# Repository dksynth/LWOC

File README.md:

# LWOC
Ornament and Crime for Loudest Warning Format

please note that there are two different spacings in use. 

The "broken grid" variant pushes two rows a bit closer together towards the screen at the bottom. This preserves the spacing of the top row at the cost of a crowded set of jacks nearer the encoders and  screen. 

IN ALMOST ALL CASES (unless you've made your own panels) you will want to use the main files found in the main repository.

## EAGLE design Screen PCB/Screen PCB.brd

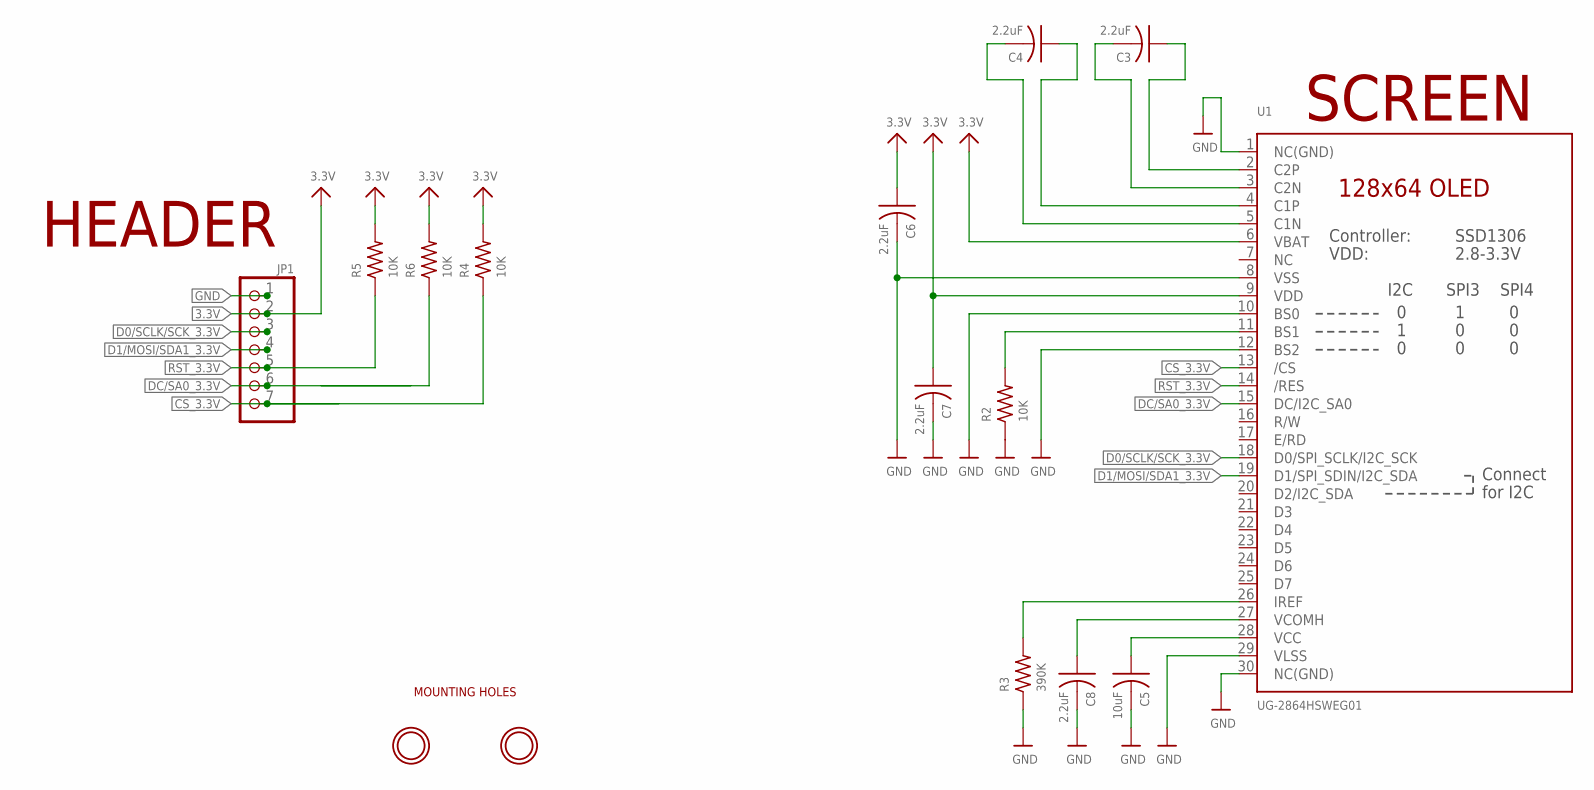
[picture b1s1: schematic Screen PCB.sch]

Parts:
C3, C4, C6, C7, C8: 2.2uF; C0805
C5: 10uF; C0805
JP1: HEADER-1X7ROUND; 1X07_ROUND
R2, R4, R5, R6: 10K; R0805
R3: 390K; R0805
U1: UG-2864HSWEG01; UG-2864HSWEG01_1.3_WRAPAROUND
U$23, U$26: MOUNTINGHOLE2.5; MOUNTINGHOLE_2.5_PLATED

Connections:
3.3V: C6.1, C7.1, JP1.2, R4.2, R5.2, R6.2, U1.6 (VBAT), U1.9 (VDD)
CS_3.3V: JP1.7, R4.1, U1.13 (/CS)
D0/SCLK/SCK_3.3V: JP1.3, U1.18 (D0/SPI_SCLK/I2C_SCK)
D1/MOSI/SDA1_3.3V: JP1.4, U1.19 (D1/SPI_SDIN/I2C_SDA)
DC/SA0_3.3V: JP1.6, R6.1, U1.15 (DC/I2C_SA0)
GND: C5.2, C6.2, C7.2, C8.2, JP1.1, R2.1, R3.1, U1.1 (NC(GND)), U1.8 (VSS), U1.10 (BS0), U1.12 (BS2), U1.29 (VLSS), U1.30 (NC(GND))
unnamed: R2.2, U1.11 (BS1)
unnamed: R3.2, U1.26 (IREF)
unnamed: C4.1, U1.4 (C1P)
unnamed: C3.2, U1.3 (C2N)
unnamed: C3.1, U1.2 (C2P)
unnamed: C4.2, U1.5 (C1N)
unnamed: C5.1, U1.28 (VCC)
unnamed: C8.1, U1.27 (VCOMH)
RST_3.3V: JP1.5, R5.1, U1.14 (/RES)

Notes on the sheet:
MOUNTING HOLES
SCREEN
HEADER

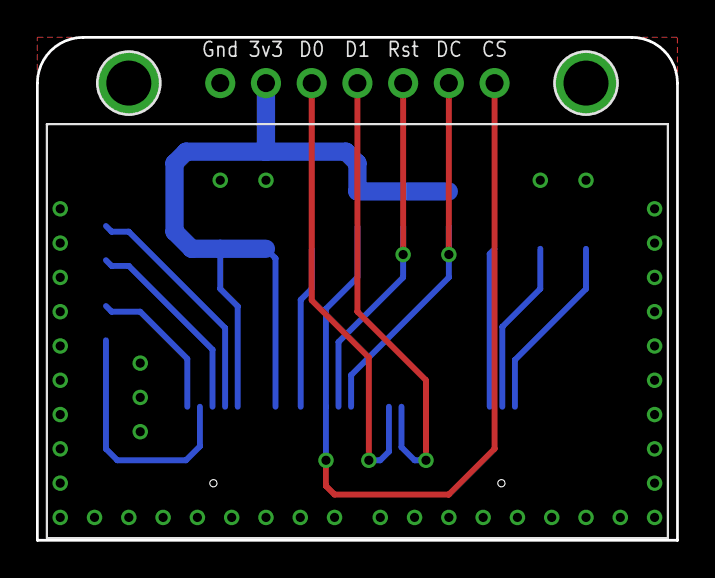
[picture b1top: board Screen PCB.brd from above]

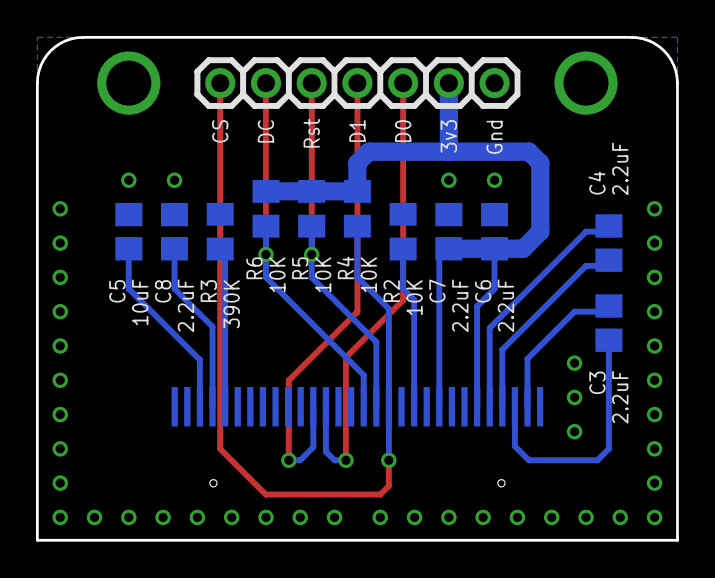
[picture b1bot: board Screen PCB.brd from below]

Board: 2 copper layers, 35.6 x 27.9 mm, 15 parts (11 on the bottom side), 15 nets.

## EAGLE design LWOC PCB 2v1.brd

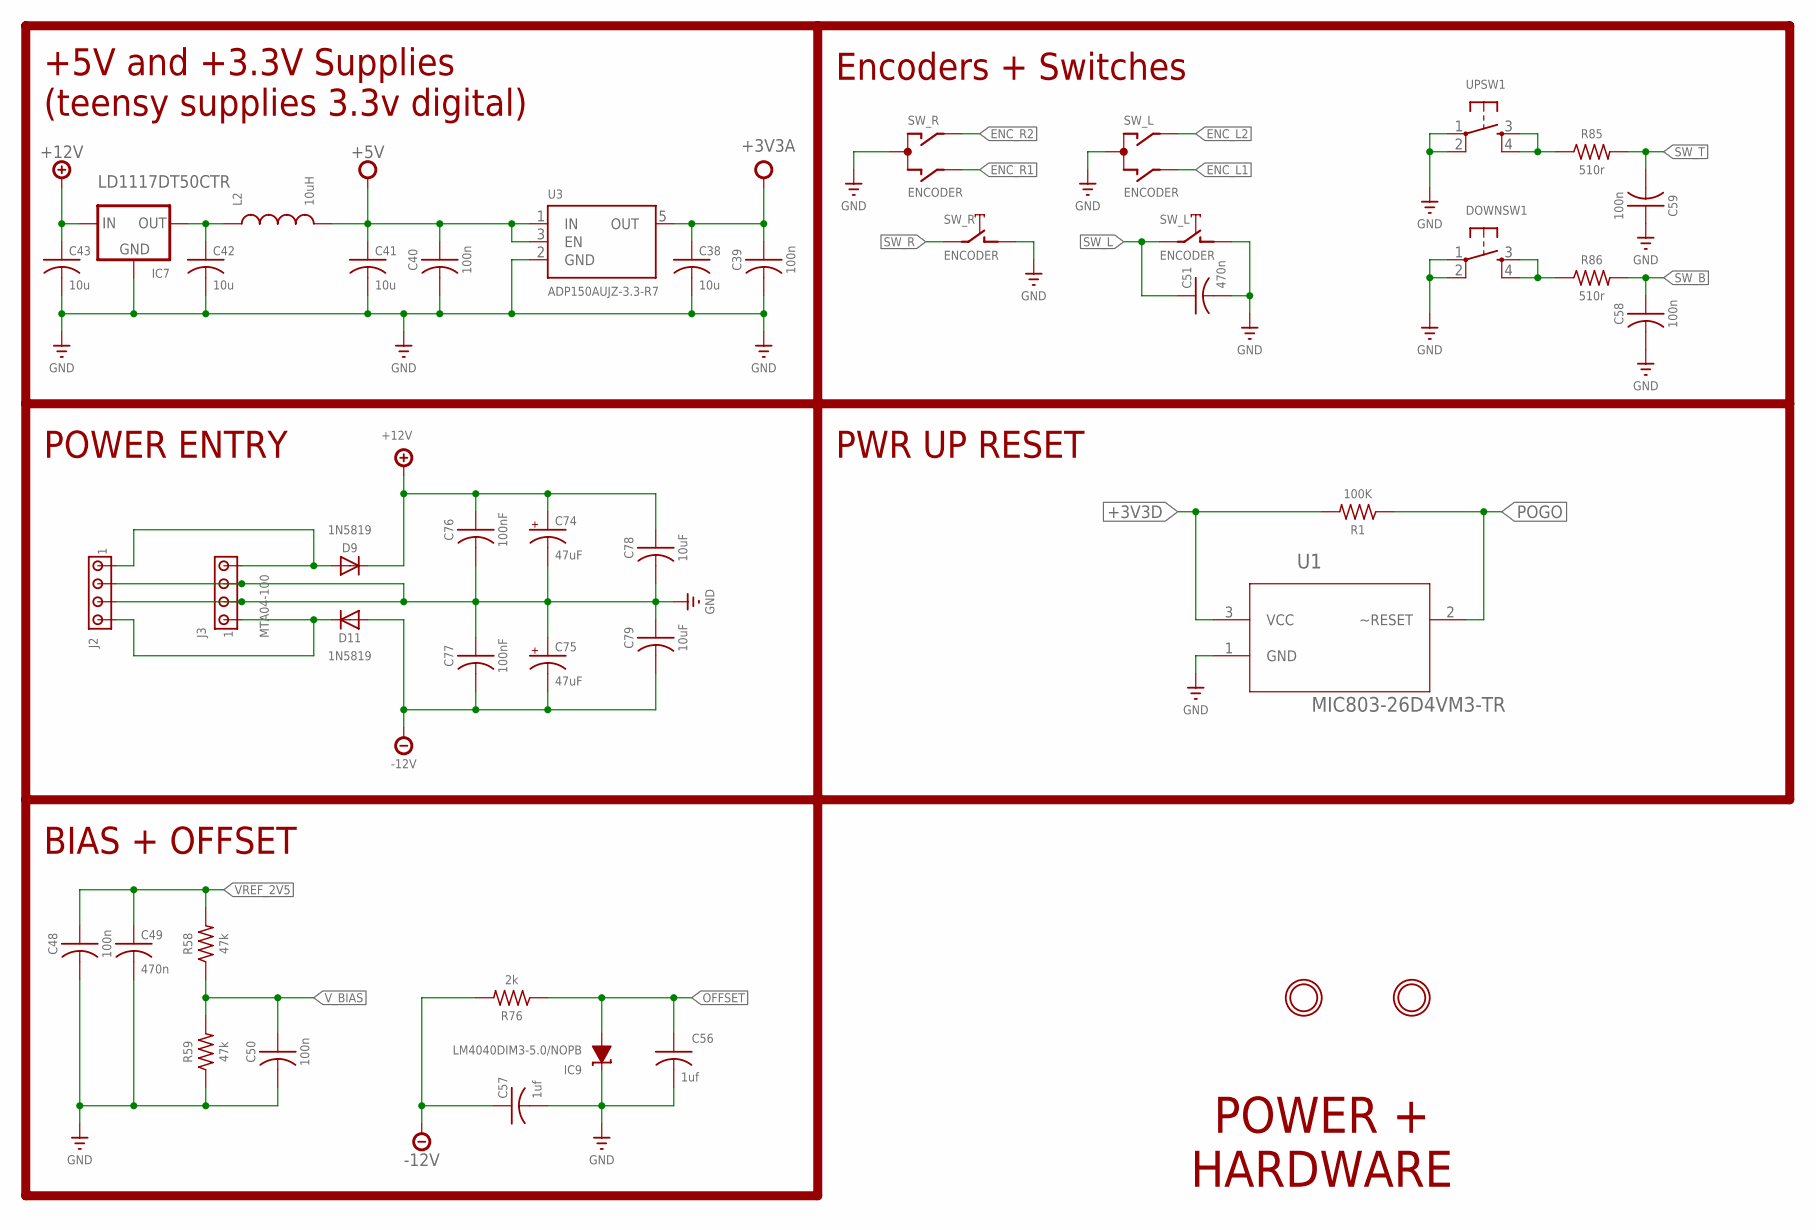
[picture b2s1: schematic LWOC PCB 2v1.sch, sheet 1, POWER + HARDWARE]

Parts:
C38, C41, C42, C43: 10u; C1206K
C39, C40, C48, C50, C58, C59: 100n; RCL_C0603K
C49: 470n; RCL_C0603K
C51: 470n; C0805K
C56, C57: 1uf; C0805K
C74, C75: 47uF; RCL_E2,5-6
C76, C77: 100nF; RCL_C0603K
C78, C79: 10uF; RCL_C1210
D9, D11: 1N5819; DIODE_SOD323-W
DOWNSW1: SPARKFUN_TAC_SWITCHPTH; SPARKFUN_TACTILE-PTH
IC7: LD1117DT50CTR; TO252
IC9: LM4040DIM3-5.0/NOPB; DBZ_R-PDSO-G3
J2: MTA04-156; 1X4MTA
J3: MTA04-100; 1X04MTA
L2: 10uH; 1210
R1: 100K; RCL_R0603
R58, R59: 47k; RCL_R0603
R76: 2k; RCL_R0603
R85, R86: 510r; RCL_R0603
SW_L: ENCODER; OG-ENCODER_ALPS_EC12E_SW
SW_R: ENCODER; OG-ENCODER_ALPS_EC12E_SW
U1: MIC803-26D4VM3-TR; SOT95P232X110-3N
U3: ADP150AUJZ-3.3-R7; SOT23-5
U$23, U$26: MOUNTINGHOLE2.5; MOUNTINGHOLE_2.5_PLATED
UPSW1: SPARKFUN_TAC_SWITCHPTH; SPARKFUN_TACTILE-PTH

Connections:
+3V3A: C38.1, C39.1, U3.5 (OUT); also elsewhere on the board
+3V3D: R1.2, U1.3 (VCC); also elsewhere on the board
+5V: C40.1, C41.1, L2.2, U3.1 (IN), U3.3 (EN); also elsewhere on the board
+12V: C43.1, C74.+, C76.1, C78.1, D9.C, IC7.2 (IN); also elsewhere on the board
-12V: C57.1, C75.-, C77.2, C79.2, D11.A, R76.2; also elsewhere on the board
ENC_L1: SW_L.B; also elsewhere on the board
ENC_L2: SW_L.A; also elsewhere on the board
ENC_R1: SW_R.B; also elsewhere on the board
ENC_R2: SW_R.A; also elsewhere on the board
GND: C38.2, C39.2, C40.2, C41.2, C42.2, C43.2, C48.2, C49.2, C50.2, C51.2, C56.2, C57.2, C58.2, C59.1, C74.-, C75.+, C76.2, C77.1, C78.2, C79.1, DOWNSW1.1, DOWNSW1.2, IC7.1 (GND), IC9.1 (C), J2.2, J2.3, J3.2 (3), J3.3 (2), R59.1, SW_L.C, SW_L.D (1), SW_R.C, SW_R.D (1), U1.1 (GND), U3.2 (GND), UPSW1.1, UPSW1.2; also elsewhere on the board
unnamed: C42.1, IC7.3 (OUT), L2.1
unnamed: R85.1, UPSW1.3, UPSW1.4
unnamed: DOWNSW1.3, DOWNSW1.4, R86.1
unnamed: D11.C, J2.4, J3.4 (1)
unnamed: D9.A, J2.1, J3.1 (4)
OFFSET: C56.1, IC9.2 (A), R76.1; also elsewhere on the board
POGO: R1.1, U1.2 (~RESET)
SW_B: C58.1, R86.2; also elsewhere on the board
SW_L: C51.1, SW_L.E (2); also elsewhere on the board
SW_R: SW_R.E (2); also elsewhere on the board
SW_T: C59.2, R85.2; also elsewhere on the board
VREF_2V5: C48.1, C49.1, R58.2; also elsewhere on the board
V_BIAS: C50.1, R58.1, R59.2; also elsewhere on the board

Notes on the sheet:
POWER + HARDWARE
+5V and +3.3V Supplies (teensy supplies 3.3v digital)
Encoders + Switches
PWR UP RESET
POWER ENTRY
BIAS + OFFSET

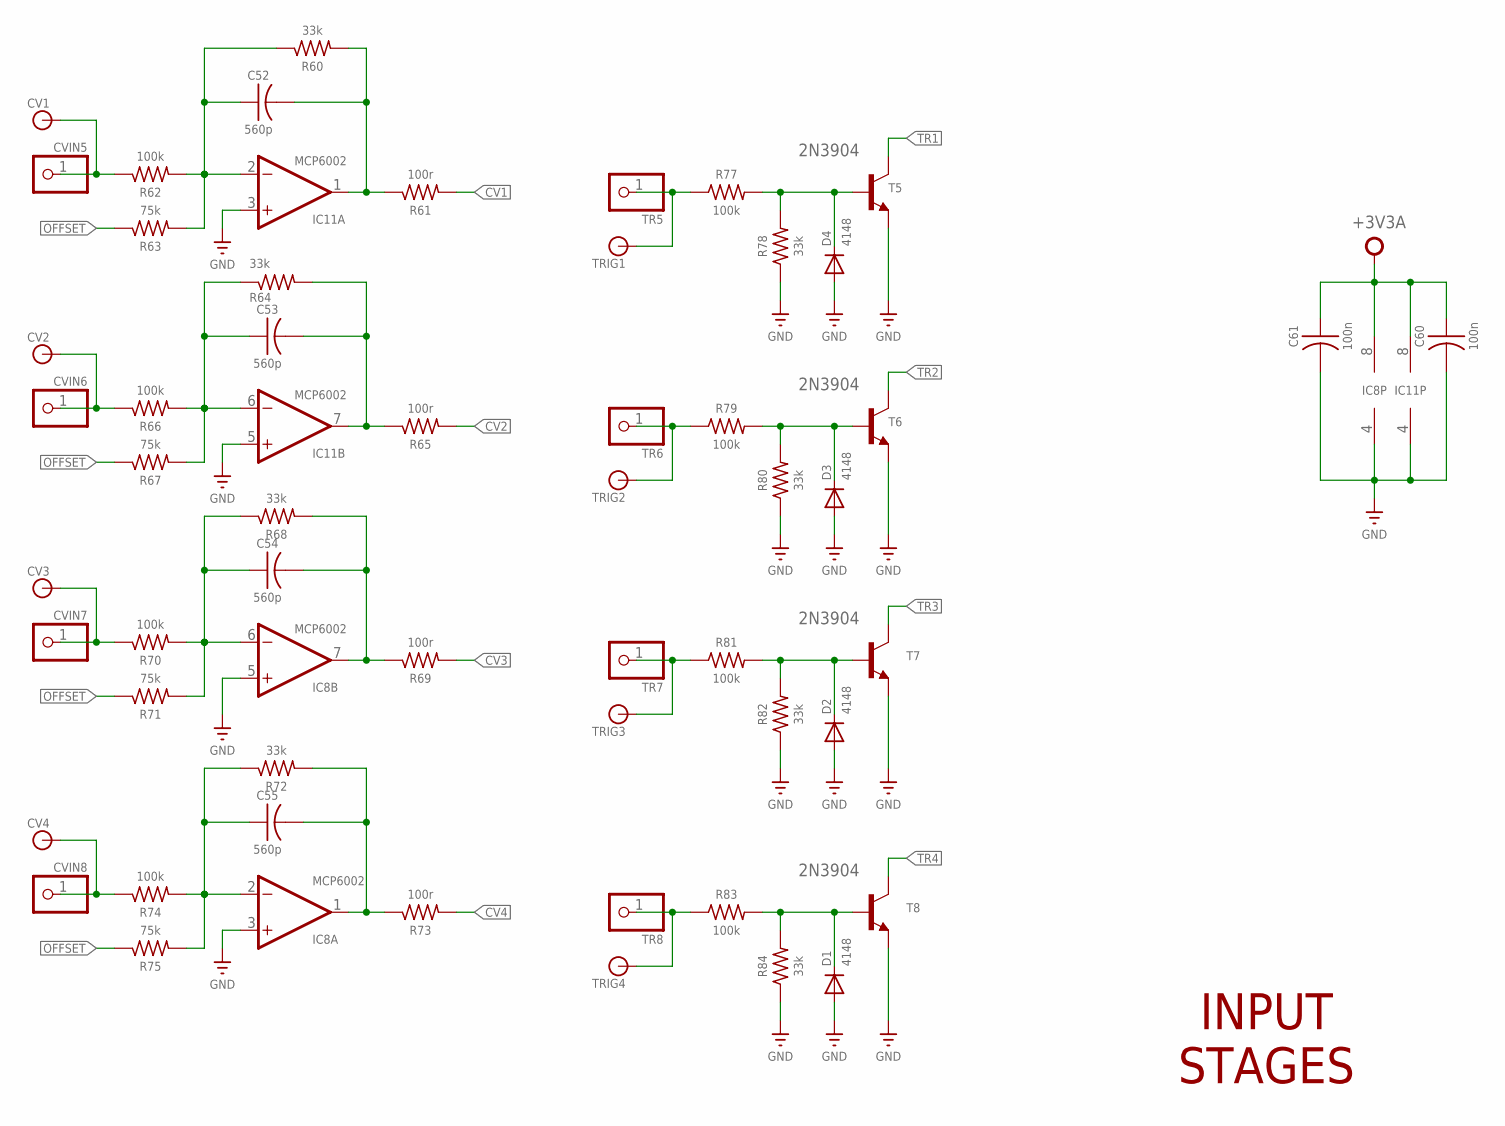
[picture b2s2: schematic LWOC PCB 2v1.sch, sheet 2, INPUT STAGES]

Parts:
C52, C53, C54, C55: 560p; RCL_C0603K
C60, C61: 100n; RCL_C0603K
CV1, CV2, CV3, CV4: BANANA_CONN
CVIN5, CVIN6, CVIN7, CVIN8: PINHD-1X1; 1X01
D1, D2, D3, D4: 4148; DIODE_SOD323-W
IC8, IC11: MCP6002; GM-ICS_SO08
R60, R64, R68, R72, R78, R80, R82, R84: 33k; RCL_R0603
R61, R65, R69, R73: 100r; RCL_R0603
R62, R66, R70, R74, R77, R79, R81, R83: 100k; RCL_R0603
R63, R67, R71, R75: 75k; RCL_R0603
T5, T6, T7, T8: 2N3904; TRANSISTOR_SOT23-BEC
TR5, TR6, TR7, TR8: PINHD-1X1; 1X01
TRIG1, TRIG2, TRIG3, TRIG4: BANANA_CONN

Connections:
+3V3A: C60.1, C61.1, IC8.8 (V+), IC11.8 (V+); also elsewhere on the board
CV1: R61.2; also elsewhere on the board
CV2: R65.2; also elsewhere on the board
CV3: R69.2; also elsewhere on the board
CV4: R73.2; also elsewhere on the board
GND: C60.2, C61.2, D1.A, D2.A, D3.A, D4.A, IC8.3 (+IN), IC8.4 (V-), IC8.5 (+IN), IC11.3 (+IN), IC11.4 (V-), IC11.5 (+IN), R78.1, R80.1, R82.1, R84.1, T5.E, T6.E, T7.E, T8.E; also elsewhere on the board
unnamed: CV1.P$1, CVIN5.1, R62.1
unnamed: C52.1, IC11.2 (-IN), R60.1, R62.2, R63.2
unnamed: C52.2, IC11.1 (OUT), R60.2, R61.1
unnamed: CV2.P$1, CVIN6.1, R66.1
unnamed: C53.1, IC11.6 (-IN), R64.1, R66.2, R67.2
unnamed: C53.2, IC11.7 (OUT), R64.2, R65.1
unnamed: CV3.P$1, CVIN7.1, R70.1
unnamed: C54.1, IC8.6 (-IN), R68.1, R70.2, R71.2
unnamed: C54.2, IC8.7 (OUT), R68.2, R69.1
unnamed: CV4.P$1, CVIN8.1, R74.1
unnamed: C55.1, IC8.2 (-IN), R72.1, R74.2, R75.2
unnamed: C55.2, IC8.1 (OUT), R72.2, R73.1
unnamed: R77.1, TR5.1, TRIG1.P$1
unnamed: R79.1, TR6.1, TRIG2.P$1
unnamed: R81.1, TR7.1, TRIG3.P$1
unnamed: D1.C, R83.2, R84.2, T8.B
unnamed: D2.C, R81.2, R82.2, T7.B
unnamed: D3.C, R79.2, R80.2, T6.B
unnamed: D4.C, R77.2, R78.2, T5.B
unnamed: R83.1, TR8.1, TRIG4.P$1
OFFSET: R63.1, R67.1, R71.1, R75.1; also elsewhere on the board
TR1: T5.C; also elsewhere on the board
TR2: T6.C; also elsewhere on the board
TR3: T7.C; also elsewhere on the board
TR4: T8.C; also elsewhere on the board

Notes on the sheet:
INPUT STAGES

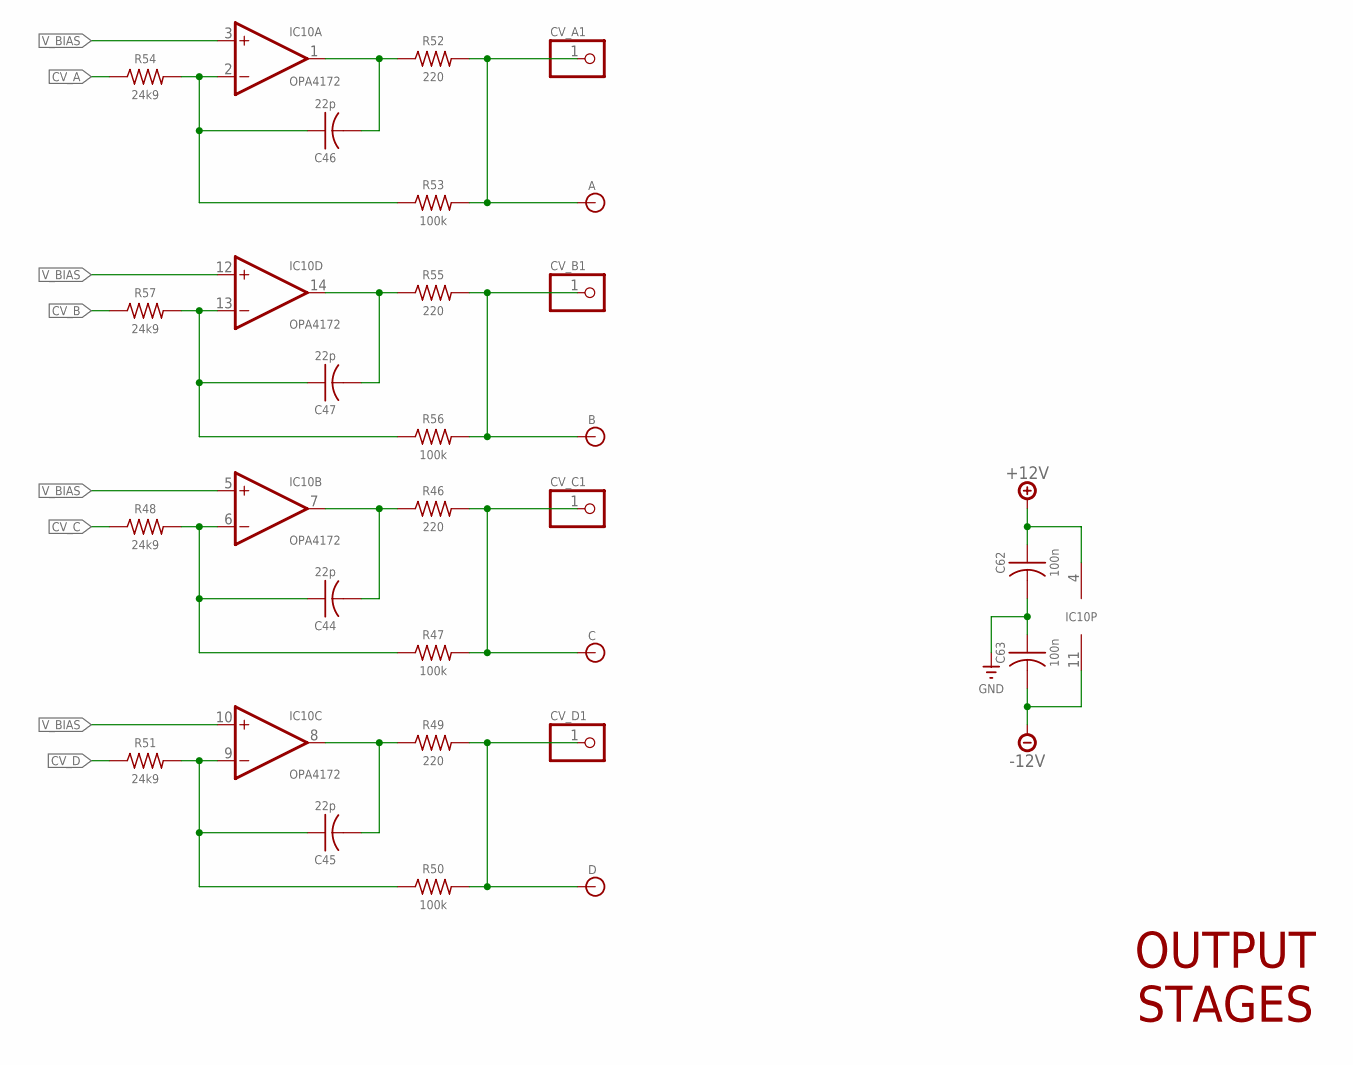
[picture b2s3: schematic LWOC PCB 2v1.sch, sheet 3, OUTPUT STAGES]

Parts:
A: BANANA_CONN
B: BANANA_CONN
C: BANANA_CONN
C44, C45, C46, C47: 22p; RCL_C0603K
C62, C63: 100n; RCL_C0603K
CV_A1: PINHD-1X1; 1X01
CV_B1: PINHD-1X1; 1X01
CV_C1: PINHD-1X1; 1X01
CV_D1: PINHD-1X1; 1X01
D: BANANA_CONN
IC10: OPA4172; GM-ICS_SO14
R46, R49, R52, R55: 220; RCL_R0603
R47, R50, R53, R56: 100k; RCL_R0603
R48, R51, R54, R57: 24k9; RCL_R0603

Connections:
+12V: C62.1, IC10.4 (V+); also elsewhere on the board
-12V: C63.2, IC10.11 (V-); also elsewhere on the board
CV_A: R54.1; also elsewhere on the board
CV_B: R57.1; also elsewhere on the board
CV_C: R48.1; also elsewhere on the board
CV_D: R51.1; also elsewhere on the board
GND: C62.2, C63.1; also elsewhere on the board
unnamed: C44.1, IC10.6 (-IN), R47.1, R48.2
unnamed: C44.2, IC10.7 (OUT), R46.1
unnamed: C45.1, IC10.9 (-IN), R50.1, R51.2
unnamed: C45.2, IC10.8 (OUT), R49.1
unnamed: C46.1, IC10.2 (-IN), R53.1, R54.2
unnamed: C46.2, IC10.1 (OUT), R52.1
unnamed: C47.1, IC10.13 (-IN), R56.1, R57.2
unnamed: C47.2, IC10.14 (OUT), R55.1
unnamed: B.P$1, CV_B1.1, R55.2, R56.2
unnamed: CV_D1.1, D.P$1, R49.2, R50.2
unnamed: A.P$1, CV_A1.1, R52.2, R53.2
unnamed: C.P$1, CV_C1.1, R46.2, R47.2
V_BIAS: IC10.3 (+IN), IC10.5 (+IN), IC10.10 (+IN), IC10.12 (+IN); also elsewhere on the board

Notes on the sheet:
OUTPUT STAGES

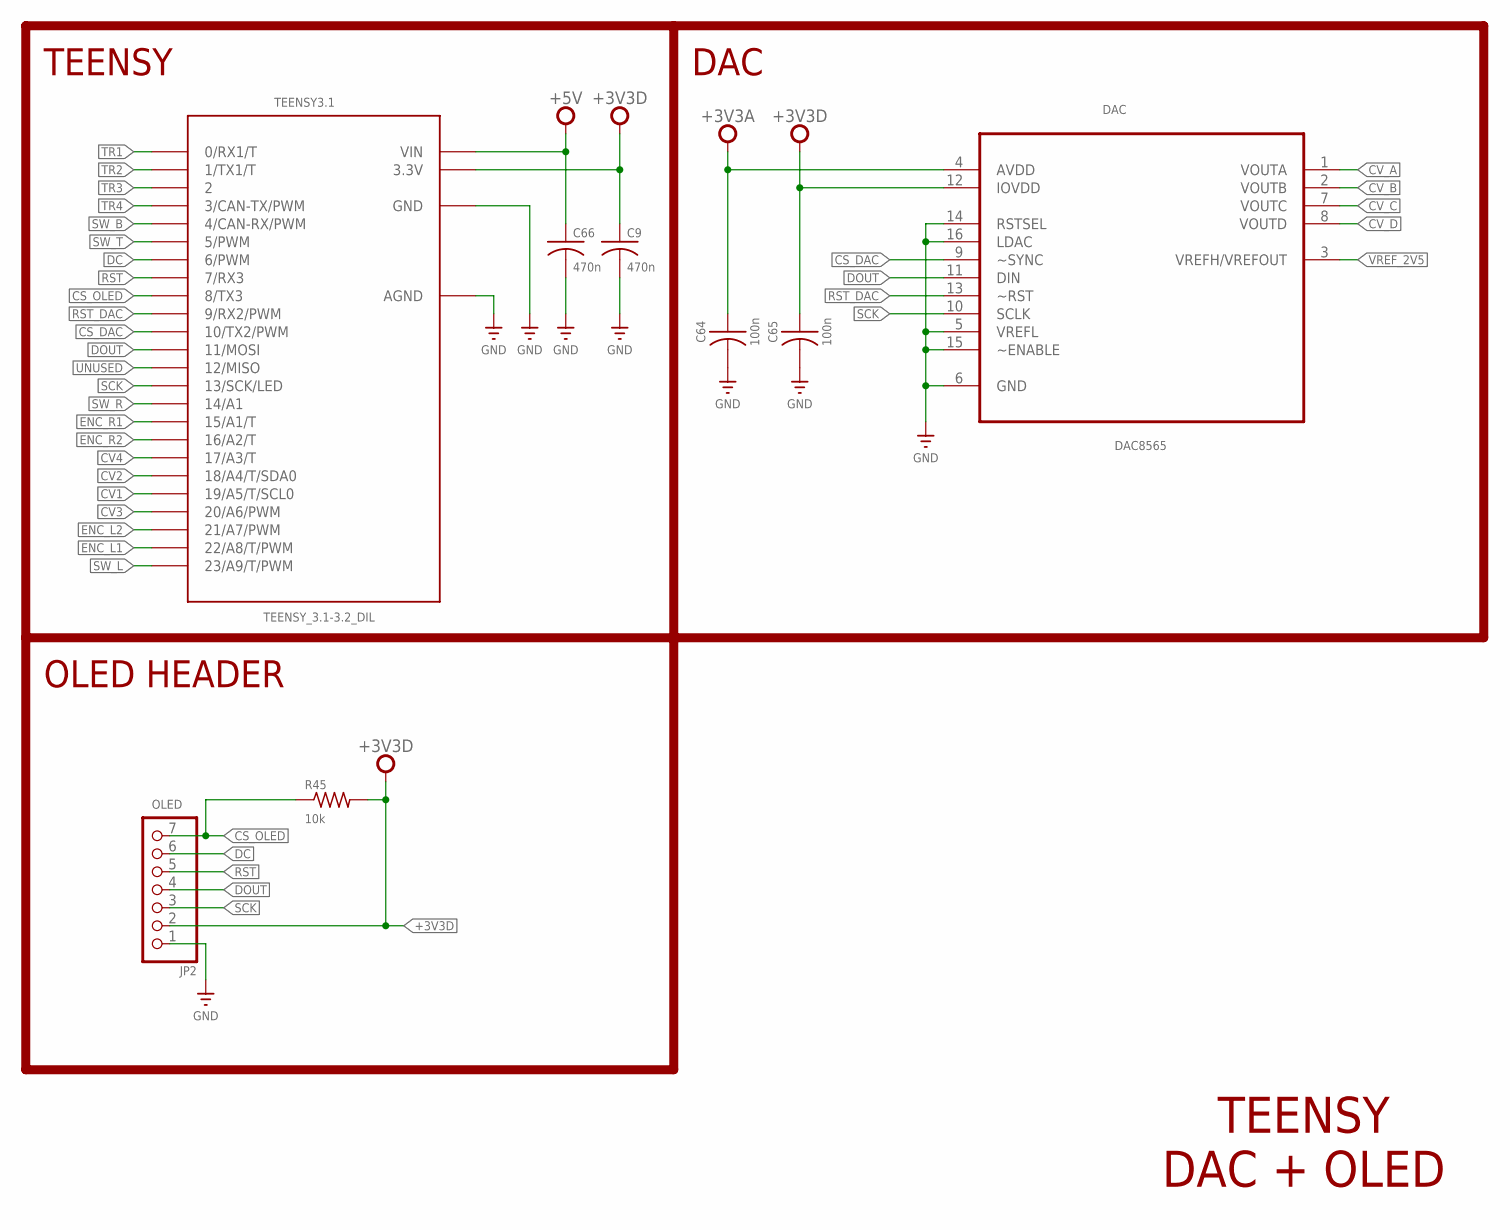
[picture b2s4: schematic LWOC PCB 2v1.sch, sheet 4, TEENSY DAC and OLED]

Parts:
C9, C66: 470n; C0805K
C64, C65: 100n; RCL_C0603K
DAC: DAC8565; SOP65P640X120-16N
JP2: OLED; 1X07-S
R45: 10k; M0805
TEENSY3.1: TEENSY_3.1-3.2_DIL; TEENSY_3.0-3.2&LC_DIL

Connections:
+3V3A: C64.1, DAC.4 (AVDD); also elsewhere on the board
+3V3D: C9.1, C65.1, DAC.12 (IOVDD), JP2.2, R45.2, TEENSY3.1.3.3V; also elsewhere on the board
+5V: C66.1, TEENSY3.1.VIN; also elsewhere on the board
CS_DAC: DAC.9 (~SYNC), TEENSY3.1.10 (10/TX2/PWM)
CS_OLED: JP2.7, R45.1, TEENSY3.1.8 (8/TX3)
CV1: TEENSY3.1.19/A5 (19/A5/T/SCL0); also elsewhere on the board
CV2: TEENSY3.1.18/A4 (18/A4/T/SDA0); also elsewhere on the board
CV3: TEENSY3.1.20/A6 (20/A6/PWM); also elsewhere on the board
CV4: TEENSY3.1.17/A3 (17/A3/T); also elsewhere on the board
CV_A: DAC.1 (VOUTA); also elsewhere on the board
CV_B: DAC.2 (VOUTB); also elsewhere on the board
CV_C: DAC.7 (VOUTC); also elsewhere on the board
CV_D: DAC.8 (VOUTD); also elsewhere on the board
DC: JP2.6, TEENSY3.1.6 (6/PWM)
DOUT: DAC.11 (DIN), JP2.4, TEENSY3.1.11 (11/MOSI)
ENC_L1: TEENSY3.1.22/A8 (22/A8/T/PWM); also elsewhere on the board
ENC_L2: TEENSY3.1.21/A7 (21/A7/PWM); also elsewhere on the board
ENC_R1: TEENSY3.1.15/A1 (15/A1/T); also elsewhere on the board
ENC_R2: TEENSY3.1.16/A2 (16/A2/T); also elsewhere on the board
GND: C9.2, C64.2, C65.2, C66.2, DAC.5 (VREFL), DAC.6 (GND), DAC.14 (RSTSEL), DAC.15 (~ENABLE), DAC.16 (LDAC), JP2.1, TEENSY3.1.AGND, TEENSY3.1.GND; also elsewhere on the board
RST: JP2.5, TEENSY3.1.7 (7/RX3)
RST_DAC: DAC.13 (~RST), TEENSY3.1.9 (9/RX2/PWM)
SCK: DAC.10 (SCLK), JP2.3, TEENSY3.1.13 (13/SCK/LED)
SW_B: TEENSY3.1.4 (4/CAN-RX/PWM); also elsewhere on the board
SW_L: TEENSY3.1.23/A9 (23/A9/T/PWM); also elsewhere on the board
SW_R: TEENSY3.1.14/A0 (14/A1); also elsewhere on the board
SW_T: TEENSY3.1.5 (5/PWM); also elsewhere on the board
TR1: TEENSY3.1.0 (0/RX1/T); also elsewhere on the board
TR2: TEENSY3.1.1 (1/TX1/T); also elsewhere on the board
TR3: TEENSY3.1.2; also elsewhere on the board
TR4: TEENSY3.1.3 (3/CAN-TX/PWM); also elsewhere on the board
UNUSED: TEENSY3.1.12 (12/MISO)
VREF_2V5: DAC.3 (VREFH/VREFOUT); also elsewhere on the board

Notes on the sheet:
TEENSY DAC + OLED
OLED HEADER
TEENSY
DAC

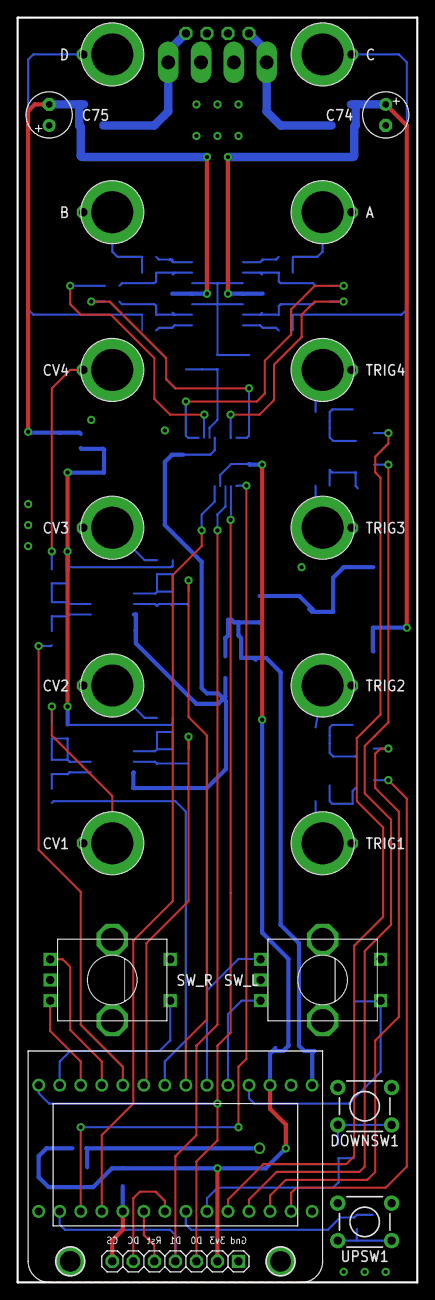
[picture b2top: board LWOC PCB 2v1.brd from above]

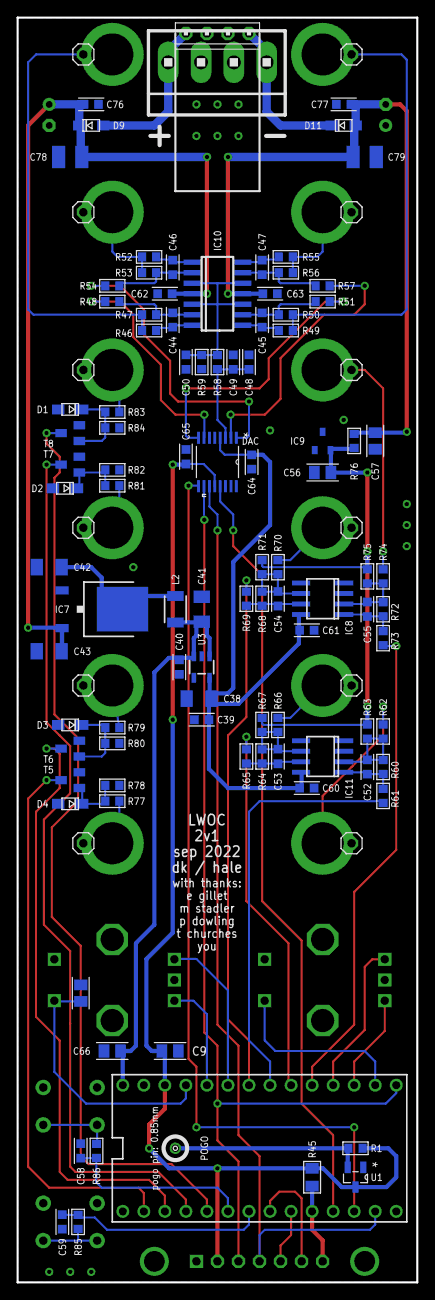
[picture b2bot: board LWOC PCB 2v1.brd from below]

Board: 2 copper layers, 48.3 x 152.7 mm, 132 parts (111 on the bottom side), 74 nets.

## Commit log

2022-09-08 Add files via upload
    LWOC 2.0 Schematic PDF
2022-09-08 Add files via upload
    LWOC 2.0 sch/brd Eagle files
2023-11-27 SCREEN

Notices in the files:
parts and their libraries:
SparkFun-Connectors: Licensing: Creative Commons ShareAlike 4.0 International - https://creativecommons.org/licenses/by-sa/4.0
supply0: Copyright (C) 2007, Bob Starr
